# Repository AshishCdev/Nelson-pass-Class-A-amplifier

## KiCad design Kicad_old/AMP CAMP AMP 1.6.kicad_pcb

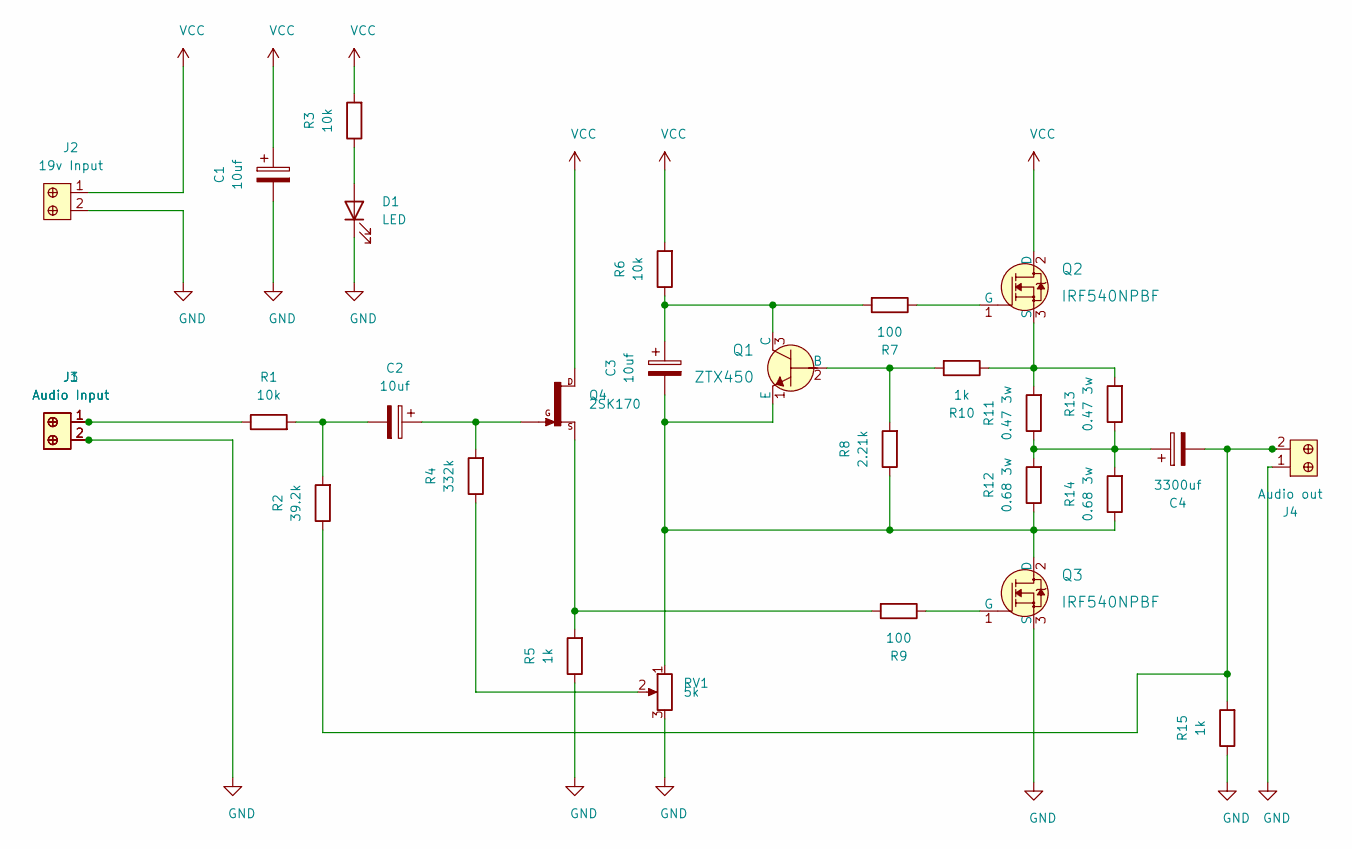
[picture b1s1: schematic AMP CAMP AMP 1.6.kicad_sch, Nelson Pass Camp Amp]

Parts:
C1, C2, C3: 10uf; R_0402_1005Metric
C4: 3300uf; R_0402_1005Metric
D1: LED; LED_1210_3225Metric_Pad1.42x2.65mm_HandSolder
J1, J3: Audio Input; Term_Block_1x2_P5.08MM; MPN OSTTC022162; Digi-Key_PN ED2609-ND
J2: 19v Input; Term_Block_1x2_P5.08MM; MPN OSTTC022162; Digi-Key_PN ED2609-ND
J4: Audio out; Term_Block_1x2_P5.08MM; MPN OSTTC022162; Digi-Key_PN ED2609-ND
Q1: ZTX450; TO-92-3; MPN ZTX450; Digi-Key_PN ZTX450-ND
Q2, Q3: IRF540NPBF; TO-220-3; MPN IRF540NPBF; Digi-Key_PN IRF540NPBF-ND
Q4: 2SK170; TO-92-3
R1, R3, R6: 10k; R_0402_1005Metric
R2: 39.2k; R_0402_1005Metric
R4: 332k; R_0402_1005Metric
R5, R10, R15: 1k; R_0402_1005Metric
R7, R9: 100; R_0402_1005Metric
R8: 2.21k; R_0402_1005Metric
R11, R13: 0.47 3w; R_0402_1005Metric
R12, R14: 0.68 3w; R_0402_1005Metric
RV1: 5k; Potentiometer_ACP_CA9-H5_Horizontal

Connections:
GND: C1.2, D1.1 (K), J1.2, J2.2, J3.2, J4.1, Q3.3 (S), R5.1, R15.1, RV1.3
unnamed: C2.1, Q4.2, R4.2
unnamed: C2.2, R1.2, R2.2
unnamed: C3.1, Q1.3 (C), R6.1, R7.2
unnamed: C3.2, Q1.1 (E), Q3.2 (D), R8.1, R12.1, R14.1, RV1.1
unnamed: C4.1, R11.1, R12.2, R13.1, R14.2
unnamed: C4.2, J4.2, R2.1, R15.2
unnamed: D1.2 (A), R3.1
unnamed: J1.1, J3.1, R1.1
unnamed: Q1.2 (B), R8.2, R10.2
unnamed: Q2.1 (G), R7.1
unnamed: Q2.3 (S), R10.1, R11.2, R13.2
unnamed: Q3.1 (G), R9.1
unnamed: Q4.3, R5.2, R9.2
unnamed: R4.1, RV1.2
VCC: C1.1, J2.1, Q2.2 (D), Q4.1, R3.2, R6.2

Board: 2 copper layers, 29 parts (0 on the bottom side), 16 nets, no tracks yet.

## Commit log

2020-09-19 Schematic done
2021-02-13 Updated the layout from PCB
2023-08-06 added more documents
